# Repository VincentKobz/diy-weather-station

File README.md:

# Weather Station :cloud: :sunrise_over_mountains: :rainbow:

## Description of the project

The goal is to build from scratch a small intelligent weather station that can be connected to **IOT** networks.

It features the following sensors:
- temperature
- humidity
- pressure
- altitude
- gas (Ammonia, Nitrogen Oxide, Alcohol, Benzene, Co2, CO ...)

This GitHub repository describes the entire project, from the choice of components to the software.

## Get started

### How to setup the code

- Clone this [repository](https://github.com/VincentKobz/diy-weather-station/).

- Add this URL `https://raw.githubusercontent.com/espressif/arduino-esp32/gh-pages/package_esp32_index.json` to the additional boards manager in your IDE.

- Install the right package for your board (for me it's an [ESP32](https://github.com/espressif/arduino-esp32)).

Arduino librairies that need to be installed:
- [PubSubClient](https://pubsubclient.knolleary.net/): for MQTT protocol.
- [MQUnifiedSensor](https://github.com/miguel5612/MQSensorsLib): for MQ135 sensor.
- [Adafruit BMP085](https://github.com/adafruit/Adafruit-BMP085-Library): for BMP180 sensor.
- [DHT sensor](https://github.com/adafruit/DHT-sensor-library): for DHT22 sensor.

Inside `global_data.h`, replace `SSID`, `SSID_PWD`, `MQTT_SERVER_IP`, `MQTT_PORT`, `MQTT_DEVICE_ID` with your values.

This file contains all GPIO and sensor configuration, as well as global variables and macros.

## Bill Of Materials

All the information on **components** (BOM) and electronic schematics: [link](bom.md)

## Electronic card schematic and PCB

All the information on custom **PCB** (Printed Circuit Board): [link](kicad/kicad.md)

## Integration to home-assistant

[Home assistant](https://www.home-assistant.io/) is an open source software for home automation. I successfully connect my DIY weather station to it with an **MQTT** broker.

- First, the **MQTT** integration needs to be configured with broker's address, port and credentials. This can be done with the user interface.

Here is an example of the `configuration.yaml` file.

```yaml
mqtt:
  - sensor:
      # DHT22 temperature
    - name: "temperature"
      device_class: temperature
      state_topic: "esp32/out/temperature"
      unit_of_measurement: "°C"
```

- Inside the `mqtt` section, a list of sensors can be added. Here I defined the name, the [`device_class`](https://www.home-assistant.io/integrations/sensor/), the name of the topic to listen and the unit of the data.

## Photos of the Weather Station V1

The project is not finished.
I will improve it in the future, with an optimized PCB, new sensors and a 3d printed case.

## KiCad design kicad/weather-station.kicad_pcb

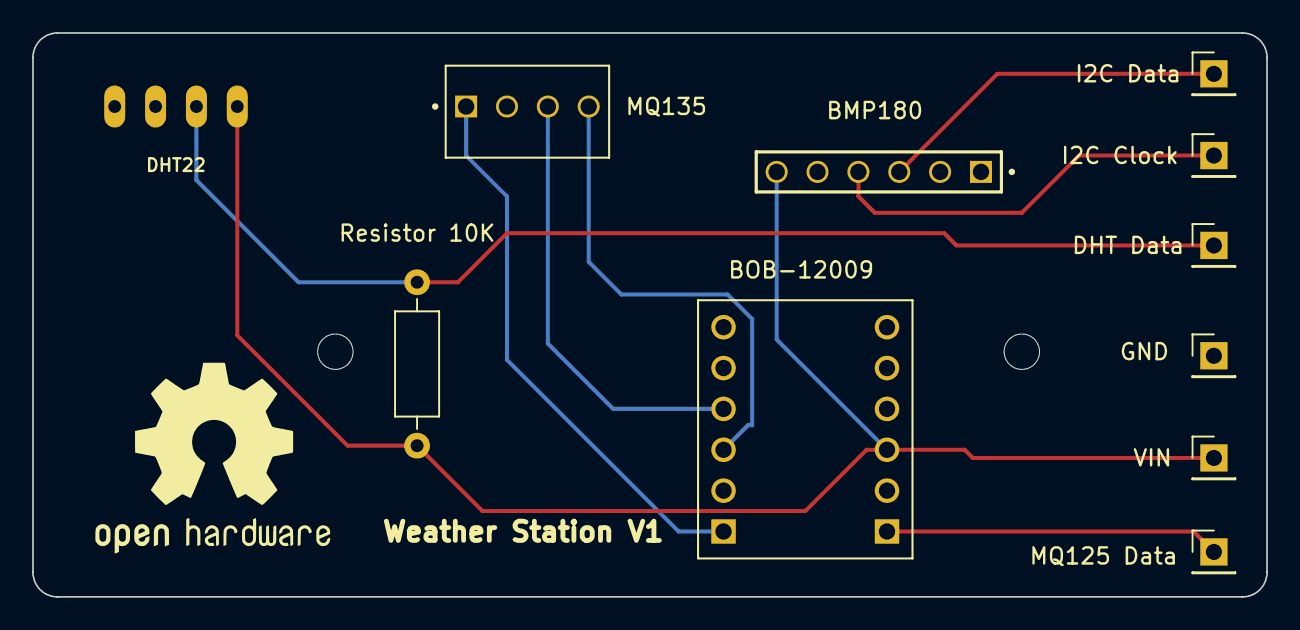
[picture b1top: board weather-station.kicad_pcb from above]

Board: 2 copper layers, 76.7 x 35.1 mm, 11 parts (0 on the bottom side), 9 nets.

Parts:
BMP180: BMP180 6PIN Header; SAMTEC_HTSW-106-07-S-S-LL
BOB-12009: BOB-12009; CONV_BOB-12009
DHT22: DHT22
DHT Data: Conn_01x01_Male; PinHeader_1x01_P2.54mm_Vertical
GND: Conn_01x01_Male; PinHeader_1x01_P2.54mm_Vertical
I2C Clock, I2C Data: Conn_01x01_Male; PinHeader_1x01_P2.54mm_Vertical
MQ125 Data: Conn_01x01_Male; PinHeader_1x01_P2.54mm_Vertical
MQ135: MQ135 4PIN Header; TE_3-641215-4
Resistor 10K: 10K; R_Axial_DIN0207_L6.3mm_D2.5mm_P10.16mm_Horizontal
VIN: Conn_01x01_Male; PinHeader_1x01_P2.54mm_Vertical

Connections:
/DHT Data: DHT22.DATA, DHT Data.1, Resistor 10K.2
/GND: BMP180.05, BOB-12009.GND_2 (GND), DHT22.GND, GND.1
/GND HV: BOB-12009.GND_1 (GND), MQ135.3
/I2C Clock: BMP180.04, I2C Clock.1
/I2C Data: BMP180.03, I2C Data.1
/MQ135 Data: BOB-12009.LV1, MQ125 Data.1
/MQ135 Data HV: BOB-12009.HV1, MQ135.1
/VCC: BMP180.06, BOB-12009.LV, DHT22.VDD, Resistor 10K.1, VIN.1
/VCC HV: BOB-12009.HV, MQ135.4

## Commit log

2023-06-26 feat: Add basic esp32 project with WiFi connection and DHT22 sensor
2023-06-28 fix: Replace magic numbers for WiFi connection with macros
2023-06-28 feat: Add connection to MQTT broker server
2023-06-28 feat: Add publish function to a specific MQTT topic
2023-06-28 fix: Remove unnecessary mqtt connection check
2023-06-28 feat: Add schematic for electrical circuit of basic weather-station
2023-06-28 update: Add electrical schematic in bom.md
2023-06-28 update: Add link to bom
2023-07-04 fix: Replace c string conversion with snprintf
2023-07-06 feat: Add support of MQ135 sensor with serial print of data
2023-07-06 fix: Add function in order to convert float to string and publish MQ135 data to the MQTT broker
2023-07-06 fix: Remove unnecessary newline and add commentary
2023-07-13 fix: Increase size of electrical circuit v1 schematic
2023-07-13 feat: Add kicad project (schematic and pcb) and documentation
2023-07-13 feat: Add Kicad documentation link to README
2023-07-13 fix: Add SnapEDA link
2023-07-13 feat: Add PCB png in kicad documentation
2023-07-17 feat: Add function to determine air quality from CO2 data
2023-07-17 feat: Improve README
2023-07-17 fix: Use snprintf instead of multiple serial printing
2023-07-17 update: Add badges to README
2023-07-22 feat: Improve code comments
2023-07-22 fix: Use snprintf for logging
2023-07-22 feat: Add comments
2023-07-22 feat: Add support of BMP180 sensor for altitude and air pressure
2023-07-22 fix: Improve comments
2023-07-22 refactor: Publish sensor data into MQTT topics
2023-08-05 fix: Add check of BMP180 sensor presence
2023-08-07 update: Add sensor to the list
2023-08-09 update: Add get started section
2023-08-09 update: Electrical circuit v1
2023-08-10 refactor: Separate mqtt and sensor services from main file
2023-08-10 fix: Add air quality function call
2023-08-10 feat: Add project images
2023-08-10 feat: Add home assistant front picture to project resources
2023-08-10 update: README.md, add pictures and home-assistant integration
2023-08-10 fix: Remove wrong sentence in README.md
2023-08-10 fix: Github badges in README.md

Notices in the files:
README.md:
License: MIT
